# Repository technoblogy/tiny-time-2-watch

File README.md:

# Tiny Time 2 Watch
A watch based on an ATtiny85 and a DS2417 RTC, showing the time analogue-style on 12 LEDs.
For more information see: http://www.technoblogy.com/show?1MG3.

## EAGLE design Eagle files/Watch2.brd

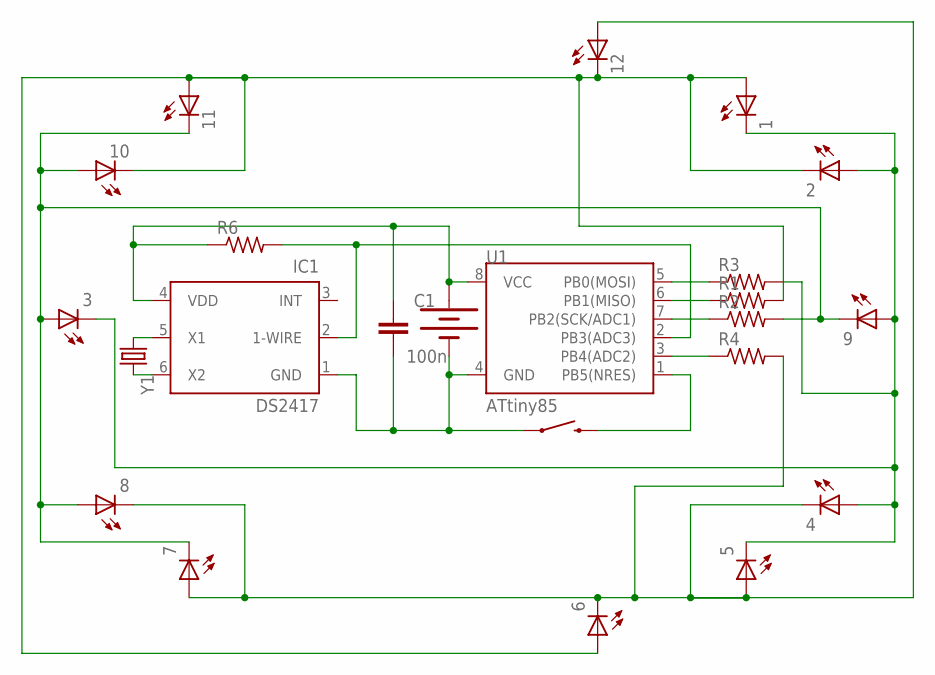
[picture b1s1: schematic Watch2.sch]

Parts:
1, 2, 3, 4, 5, 6, 7, 8, 9, 10, 11, 12: LEDCHIPLED_0805; CHIPLED_0805
BAT1: 20mm coincell; BATTCON_20MM_4LEGS
C1: 100n; 0603-CAP
IC1: DS2417; TSOC6
R1, R2, R3, R4, R6: R-US_M0805; M0805
S2: SWITCH-MOMENTARY-2SMD; TACTILE-SWITCH-SMD
U1: ATtiny85; SO08-EIAJ
Y1: CRYSTAL32-SMD-MELF; CRYSTAL-32KHZ-SMD-MELF

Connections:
INT: IC1.3 (INT)
unnamed: 1.C, 2.A, 3.C, 4.A, 5.C, 9.A, R3.2
unnamed: 4.C, 5.A, 6.C, 7.A, 8.C, 12.A, R4.2
unnamed: 3.A, 7.C, 8.A, 9.C, 10.A, 11.C, R2.2
unnamed: 1.A, 2.C, 6.A, 10.C, 11.A, 12.C, R1.2
unnamed: R3.1, U1.5 (PB0(MOSI))
unnamed: R1.1, U1.6 (PB1(MISO))
unnamed: R2.1, U1.7 (PB2(SCK/ADC1))
unnamed: R4.1, U1.3 (PB4(ADC2))
unnamed: BAT1.NEGATIVE (-), C1.2, IC1.1 (GND), S2.1, U1.4 (GND)
unnamed: S2.3 (2), U1.1 (PB5(NRES))
unnamed: IC1.2 (1-WIRE), R6.2, U1.2 (PB3(ADC3))
unnamed: BAT1.POSITIVE@1 (+), BAT1.POSITIVE@2 (+), BAT1.POSITIVE@3 (+), BAT1.POSITIVE@4 (+), C1.1, IC1.4 (VDD), R6.1, U1.8 (VCC)
unnamed: IC1.5 (X1), Y1.X1 (1)
unnamed: IC1.6 (X2), Y1.X2 (2)

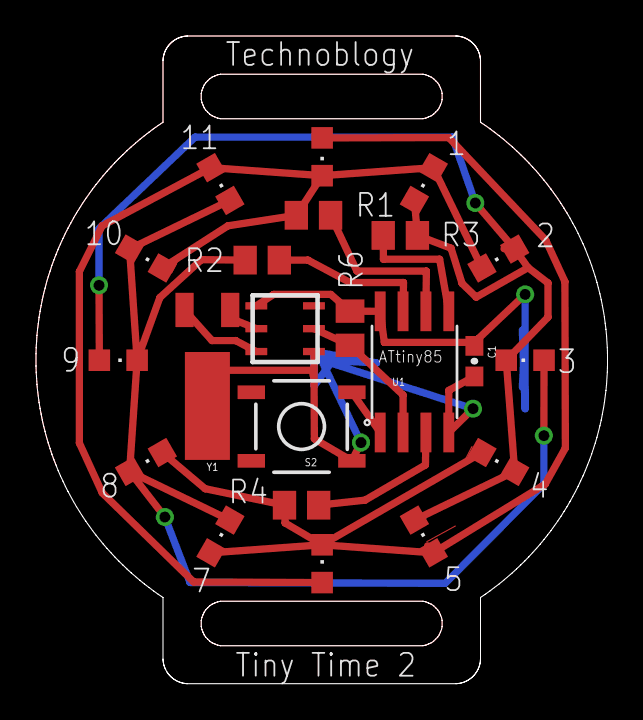
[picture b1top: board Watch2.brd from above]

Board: 2 copper layers, 31.7 x 36.0 mm, 23 parts (1 on the bottom side), 14 nets.

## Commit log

2017-04-11 Version 1 - 11th April 2017
2017-04-11 Version 1 - Eagle files
2020-12-06 Added Gerbers
2020-12-06 Reorganise
2021-03-04 Version 2 - 30th May 2019
    Fixes problems - see original article.
2021-03-04 Version 2 - 30th May 2019
    Fixes problems - see original article

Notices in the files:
parts and their libraries:
SparkFun-DigitalIC: Licensing: Creative Commons ShareAlike 4.0 International - https://creativecommons.org/licenses/by-sa/4.0
SparkFun-Capacitors: Licensing: CC v3.0 Share-Alike You are welcome to use this library for commercial purposes.
